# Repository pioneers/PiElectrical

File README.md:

# PiElectrical

This is the working repo for PiElectrical teams

1. [ToDo](#todo)
2. [Repo Structure](#repo-structure)
3. [Setup](#setup)
4. [Work Flow](#work-flow)
5. [How to Create a Gerber](#how-to-create-a-gerber)
6. [Docu Packets](#docu-packets)
7. [FAQ](#faq)
8. [Useful Links](#useful-links)
9. [Standards](#standards)

## ToDo:
* The stuff in PDB-Y16
* Convert motor controller design to KiCad
* Add and test current regulation for motor controller
* Talk to runtime and potentially use cheaper MCU for motor controller

[Back to Top](#pielectrical)

## Repo Structure:

**Boards**: Contains all necessary information about each board, including KiCad (and old Eagle) files, arduino test files, and board specific documentation.

**Bootloaders**: Contains the files necessary to burn the bootloader for boards identifying as Leonardo (Atmega32u4).

**Documentation**: All docu packets and scripts. *Fragile! Do not touch!*

**Production_Files**: Finalized gerbs and other necessary production files (BOM, CPL, etc...) sent out for fabrication.

**Images**: Place all your images in here to enhance your READMEs.

**Libraries**: Necessary KiCad files to work on PiElectrical

ToDo is on the README to keep things easier to see at first glance. GitHub issues tracker can be used as well.

[Back to Top](#pielectrical)

## Setup

<details>
    <summary>When you see an arrow like this... (click me)</summary>
        ...it indicates an expandable section. We usually include images in here as a better reference for you to follow along.
</details>

### Initial Setup of PiElectrical repo on your computer

1. Copy the URL for pioneers/PiElectrical to your clipboard: (Or here: https://github.com/pioneers/PiElectrical.git)
2. In Terminal (Mac, GNU/Linux) or Git Bash (windows), navigate to your working directory (the directory that you want to keep PiElectrical in.)
3. Clone PiElectrical by running this command: `git clone https://github.com/pioneers/PiElectrical.git`

### Installation of KiCad on your computer
1. Download the latest version of KiCad here: https://www.kicad.org/download/
2. <details>
    <summary>Run installer. Use all default settings on installer. (Click to see default settings)<br></summary>
    
</details>

### Setting up KiCad
1. Open KiCad.
2. <details>
    <summary>Depending on whether you've used KiCad before, select the appropriate option on the pop-up. (Default settings if you're new to KiCad).</summary>
    
   </details>

#### Adding Symbols
1. <details>
    <summary>Go to the <i>Preferences</i> tab, and select <i>Manage Symbol Libraries...</i></summary>
    
   </details>
2. <details>
    <summary>If this is your first time using KiCad, it will prompt you to configure the <i>Global Symbol Library</i>. It is highly recommended that you select "Copy default global symbol library table".</summary>
    
   </details>
3. <details>
    <summary>Select the folder icon near the bottom left and navigate to the <i>PiE_Symbols.kicad_sym</i> file in the <i>src</i> folder.</summary>
    
   </details>
4. <details>
    <summary>You should now see the <i>PiE_Symbols</i> in your Symbol Libraries. Make sure the "active" box is checked, and click "OK".</summary>
    
   </details>

#### Adding Footprints
1. <details>
    <summary>Go to the <i>Preferences</i> tab, and select <i>Manage Footprint Libraries...</i></summary>
    
   </details>
2. <details>
    <summary>If this is your first time using KiCad, it will prompt you to configure the <i>Global Footprint Library</i>. It is highly recommended that you select "Copy default global footprint library table".</summary>
    
   </details>
3. <details>
    <summary>Select the folder icon near the bottom left and navigate to the <i>PiE_Footprints.pretty</i> file in the <i>src</i> folder.</summary>
    
   </details>
4. <details>
    <summary>You should now see the <i>PiE_Footprints</i> in your Footprint Libraries. Make sure the "active" box is checked, and click "OK".</summary>
    
   </details>

Note that this setup instruction is based on KiCad 7.0.7, but it should still work for other versions.

[Back to Top](#pielectrical)

## Work Flow

Protocol when working on KiCad files

The revision number should be *REV \<year\>\<revision\>*. E.g. **REV 16A** for year 16 revision A.

If you are not quite familiar with git, see [Useful Links](#useful-links) for the PiE Github tutorial

**WARNING**: Do not modify PiE_Symbols.kicad_sym or PiE_Footprints.pretty without discussing it with PMs.

### Steps when working on KiCad files:

1. In Terminal (mac, GNU/Linux) or GitBash (windows), navigate to your working directory (wherever you have PiElectrical).
2. Make sure your working directory is clean: git status
3. If you haven't started your sub project: git checkout -b YOURNAME-SUBPROJECT
  3. YOUR\_NAME/SUBPROJECT is now the name of your branch
4. Do your work in KiCad.
5. Once you are at a good stopping point in your KiCad work, commit your progress:
    1. git add path/to/your/file
    2. git commit -m "Make your commit message short and with this format"
    3. **NOTE**: Commiting is like saving your file, but for all of PiE as well as your personal computer. And just like saving, Commit Early & Commit Often!
6. Repeat Steps 5 and 6 until you are finished with your EAGLE work.
7. Once you have made your last commit, push your files to the PiElectrical github repo: git push origin YOUR\_BRANCH
    - If you get a merge conflict, contact the PMs for help.
8. If **completely** done, submit a Pull Request

### Commit Message Format Conventions

* Present Tense ("Reroute power traces on team flag", not "Rerouted power traces on team flag")
* No period at the end: ("Reroute power traces on team flag", not "Reroute power traces on team flag.")
* Keep your message length to about one sentence.

### Merge Conflicts: What should I do?

Don't try to fix it yourself: Eagle files are finicky and you might break all your work!

Ask someone who knows how to deal with this, i.e. your PM or something

[Back to Top](#pielectrical)

## Generating Fabrication Outputs

1. Make sure you run the Electrical Rules Check (ERC) in the schematic and the Design Rules Checker (DRC) in the layout, and have no *red* errors. Feel free to ask PMs if you have any questions.
2. <details>
    <summary>Go to File -> Fabrication Outputs -> Gerbers (.gbr)...</summary>
    
   </details>
3. <details>
    <summary>If this is your first time using KiCad, it will prompt you to configure the <i>Global Symbol Library</i>. It is highly recommended that you select "Copy default global symbol library table".</summary>
    
   </details>
4. <details>
    <summary>Select the folder icon near the bottom left and navigate to the <i>PiE_Symbols.kicad_sym</i> file in the <i>src</i> folder.</summary>
    
   </details>
5. <details>
    <summary>You should now see the <i>PiE_Symbols</i> in your Symbol Libraries. Make sure the "active" box is checked, and click "OK".</summary>
    
   </details>

1. Open the brd file
2. Click Cam Job
3. Open pie.cam
4. Make a directory in each sensor's folder called SENSOR\_NAME-gerb
    * SENSOR\_NAME **must** be the exact name as the brd file
5. Run job, and click yes to all for the polygon issue
6. Once all the jobs are done, run `make gerb`

[Back to Top](#pielectrical)

## FAQ

Q: What's the difference between commit before I pull?

A: Do you want to keep any of the changes? Then commit those (the ones you want to keep) before you pull. Or else, the things you pull might conflict with your work, and you'll have a git disaster.

Q: I worked on my stuff, pulled, and everything I did went away!

A: As long as you committed, the PMs can recover your work for you.

Q: Why am I working on my own branch?

A: This is to keep track of pull request and board reviews on a per board basis

[Back to Top](#pielectrical)

## Useful Links

PiE's own [Github Tutorial](https://docs.google.com/a/pioneers.berkeley.edu/presentation/d/1ef5zSDMbE7dCu4XAC4dXhSV5iUd7gjCyXPjRrRvtbQI/edit?usp=sharing)

[PiElectrical Wiki](https://github.com/pioneers/PiElectrical/wiki)

[Markdown Cheatsheet](https://github.com/adam-p/markdown-here/wiki/Markdown-Cheatsheet)

[Arduino Pro Micro Pinouts](https://cdn.sparkfun.com/assets/9/c/3/c/4/523a1765757b7f5c6e8b4567.png)

[BAC DFM](http://instantdfm.bayareacircuits.com/)

Read up on the [PiE Electrical Style Rules and Guidelines](https://staff.pierobotics.org/wiki/Electrical_style_guidelines) (This is a good resource, but outdated)

[Back to Top](#pielectrical)

## Design Rules

You can find JLC's design rules here: https://jlcpcb.com/capabilities/pcb-capabilities. Please review this before ordering a PCB.

#### Some of our general rules:
- Traces **must** be multiples of 45 degrees
- Standard Pin Distance: 100 mils (2.54 mm)

#### Make sure to annotate your boards:

```
Copyright (c) 2023, Pioneers in Engineering
All rights reserved.

Design by: Justin H
This design is open source hardware.
For more information, visit 
github.com/pioneers/PiElectrical
```

[Back to Top](#pielectrical)

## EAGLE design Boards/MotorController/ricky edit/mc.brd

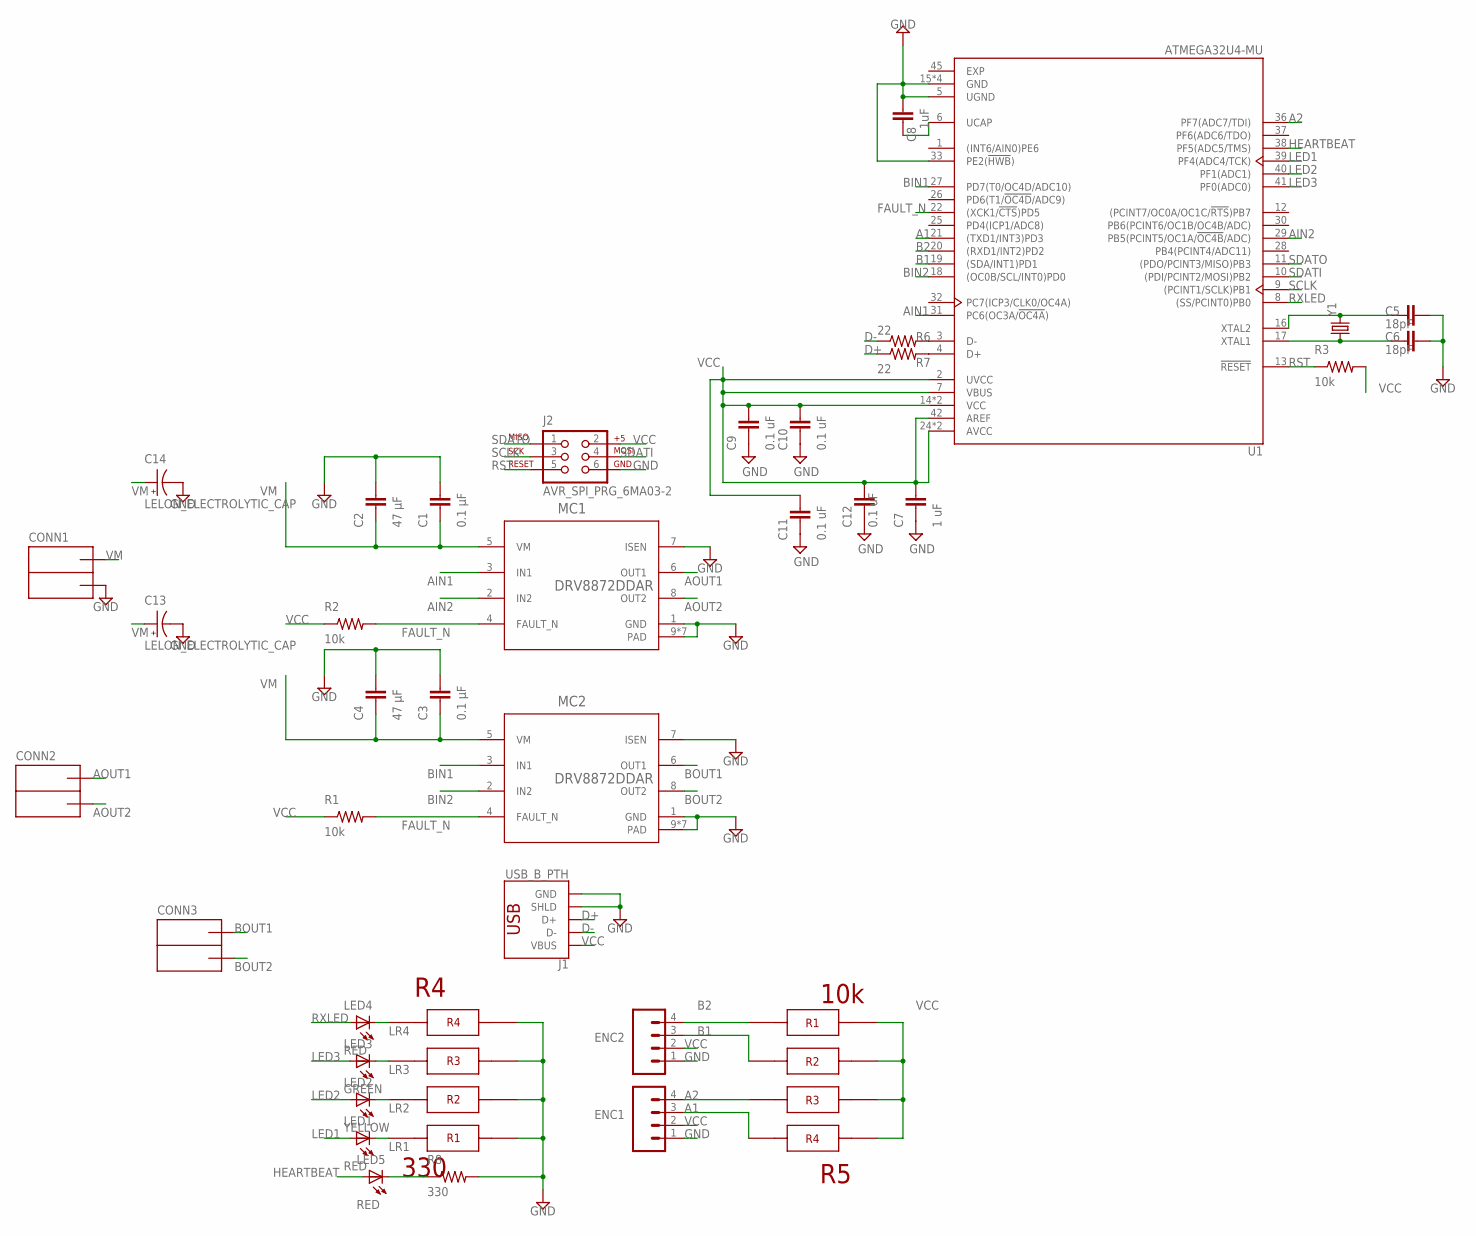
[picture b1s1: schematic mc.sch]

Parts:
C1, C3: 0.1 µF; 0603-CAP
C2, C4: 47 µF; 1206
C5, C6: 18pF; 0603-CAP
C7: 1 uF; 0603-CAP
C8: 1uF; 0603-CAP
C9, C10, C11, C12: 0.1 uF; 0402-CAP
C13, C14: LELON_ELECTROLYTIC_CAP; LELON_CAP
CONN1, CONN2, CONN3: ANDERSONVERTICAL; ANDERSON_VERTICAL
ENC1, ENC2: M041X04-MTA; 1X04-MTA
J1: USB_B_PTH; USB-B-PTH
J2: AVR_SPI_PRG_6MA03-2; MA03-2
LED1, LED4, LED5: RED; LED-0805
LED2: YELLOW; LED-0805
LED3: GREEN; LED-0805
MC1, MC2: DRV8872DDAR; DDA0008H_N_TEX
R1, R2, R3: 10k; R0603
R4: 330; 4X-0603
R5: 10k; 4X-0603
R6, R7: 22; R0603
R8: 330; R0603
U1: ATMEGA32U4-MU; QFN50P700X700X100-45N
Y1: CRYSTAL; CRYSTAL-SMD-5.0X3.2-2PIN

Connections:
A1: ENC1.3, R5.4, U1.21 ((TXD1/INT3)PD3)
A2: ENC1.4, R5.3, U1.36 (PF7(ADC7/TDI))
AIN1: MC1.3 (IN1), U1.31 (PC6(OC3A/!OC4A!))
AIN2: MC1.2 (IN2), U1.29 (PB5(PCINT5/OC1A/!OC4B!/ADC))
AOUT1: CONN2.PIN2 (OUTA), MC1.6 (OUT1)
AOUT2: CONN2.PIN1 (OUTB), MC1.8 (OUT2)
B1: ENC2.3, R5.2, U1.19 ((SDA/INT1)PD1)
B2: ENC2.4, R5.1, U1.20 ((RXD1/INT2)PD2)
BIN1: MC2.3 (IN1), U1.27 (PD7(T0/OC4D/ADC10))
BIN2: MC2.2 (IN2), U1.18 ((OC0B/SCL/INT0)PD0)
BOUT1: CONN3.PIN2 (OUTA), MC2.6 (OUT1)
BOUT2: CONN3.PIN1 (OUTB), MC2.8 (OUT2)
D+: J1.D+, R7.1
D-: J1.D-, R6.1
FAULT_N: MC1.4 (FAULT_N), MC2.4 (FAULT_N), R1.2, R2.2, U1.22 ((XCK1/!CTS!)PD5)
GND: C1.2, C2.2, C3.2, C4.2, C5.2, C6.2, C7.1, C8.2, C9.1, C10.1, C11.1, C12.1, C13.P$2 (-), C14.P$2 (-), CONN1.PIN1 (OUTB), ENC1.1, ENC2.1, J1.GND, J1.SHLD1 (SHLD), J1.SHLD2 (SHLD), J2.6, MC1.1 (GND), MC1.7 (ISEN), MC1.9 (PAD), MC1.P$1 (PAD), MC1.P$2 (PAD), MC1.P$3 (PAD), MC1.P$4 (PAD), MC1.P$5 (PAD), MC1.P$6 (PAD), MC2.1 (GND), MC2.7 (ISEN), MC2.9 (PAD), MC2.P$1 (PAD), MC2.P$2 (PAD), MC2.P$3 (PAD), MC2.P$4 (PAD), MC2.P$5 (PAD), MC2.P$6 (PAD), R4.1, R4.2, R4.3, R4.4, R8.2, U1.5 (UGND), U1.15 (GND), U1.23 (GND), U1.33 (PE2(!HWB!)), U1.35 (GND), U1.43 (GND)
HEARTBEAT: LED5.A, U1.38 (PF5(ADC5/TMS))
LED1: LED1.A, U1.39 (PF4(ADC4/TCK))
LED2: LED2.A, U1.40 (PF1(ADC1))
LED3: LED3.A, U1.41 (PF0(ADC0))
LR1: LED1.C, R4.8
LR2: LED2.C, R4.7
LR3: LED3.C, R4.6
LR4: LED4.C, R4.5
unnamed: C6.1, U1.17 (XTAL1), Y1.P$2 (2)
unnamed: R7.2, U1.4 (D+)
unnamed: R6.2, U1.3 (D-)
unnamed: C8.1, U1.6 (UCAP)
unnamed: C5.1, U1.16 (XTAL2), Y1.P$1 (1)
unnamed: LED5.C, R8.1
RST: J2.5, R3.1, U1.13 (!RESET!)
RXLED: LED4.A, U1.8 ((SS/PCINT0)PB0)
SCLK: J2.3, U1.9 ((PCINT1/SCLK)PB1)
SDATI: J2.4, U1.10 ((PDI/PCINT2/MOSI)PB2)
SDATO: J2.1, U1.11 ((PDO/PCINT3/MISO)PB3)
VCC: C7.2, C9.2, C10.2, C11.2, C12.2, ENC1.2, ENC2.2, J1.VBUS, J2.2, R1.1, R2.1, R3.2, R5.5, R5.6, R5.7, R5.8, U1.2 (UVCC), U1.7 (VBUS), U1.14 (VCC), U1.24 (AVCC), U1.34 (VCC), U1.42 (AREF), U1.44 (AVCC)
VM: C1.1, C2.1, C3.1, C4.1, C13.P$1 (+), C14.P$1 (+), CONN1.PIN2 (OUTA), MC1.5 (VM), MC2.5 (VM)

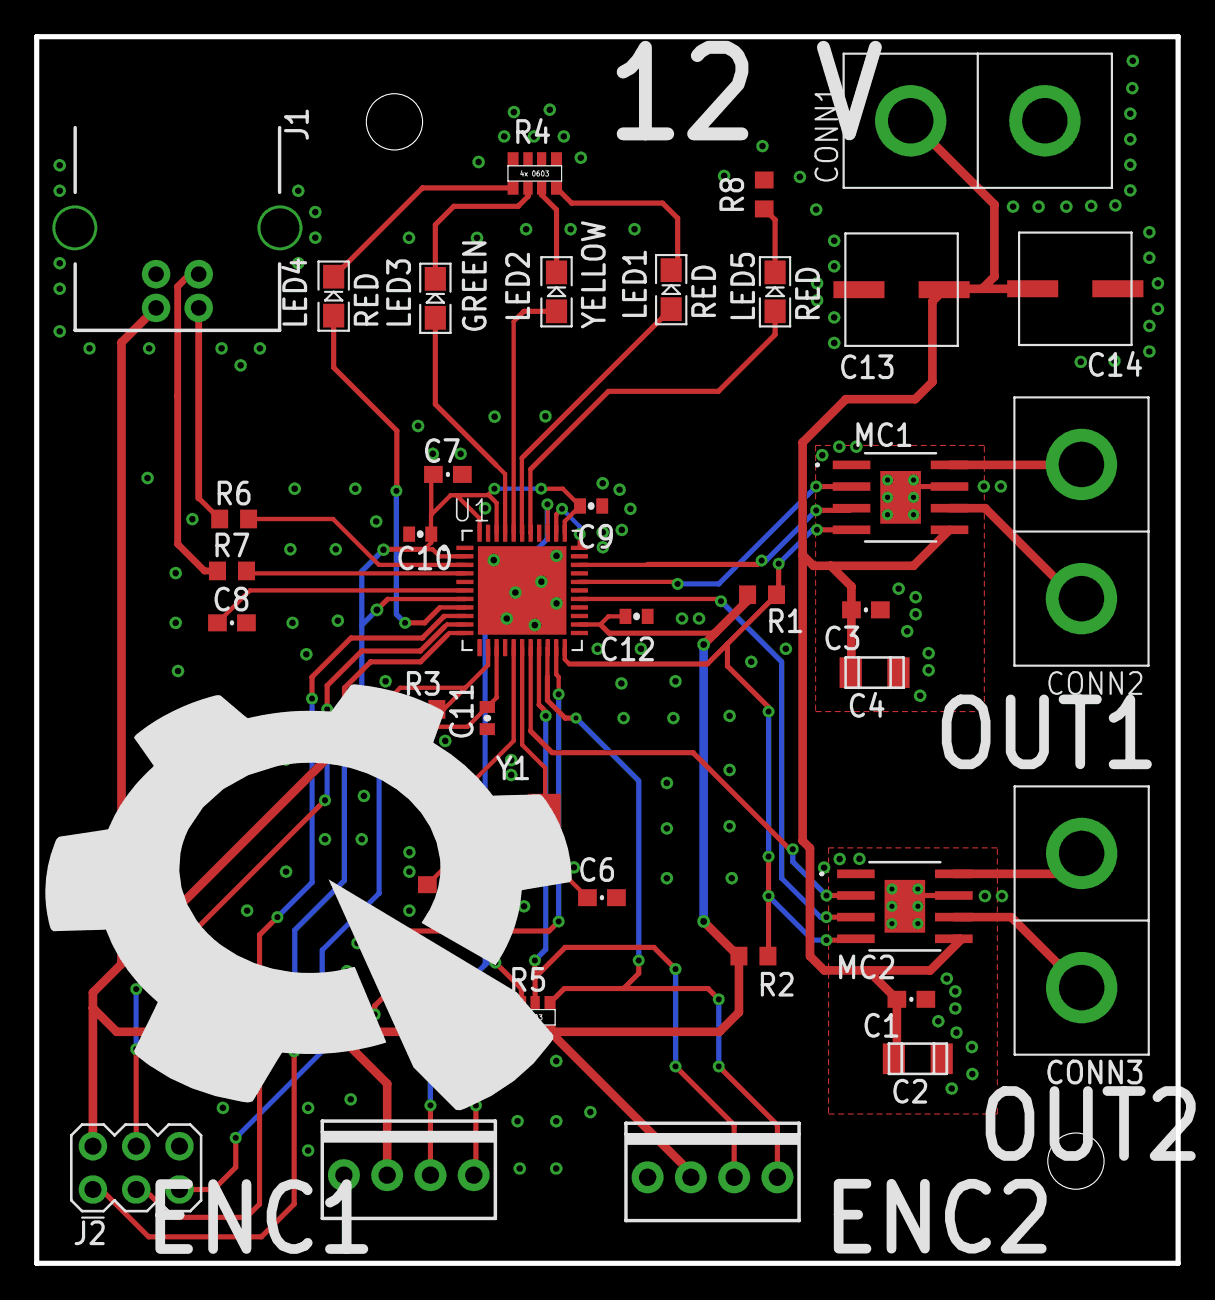
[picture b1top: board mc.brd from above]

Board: 2 copper layers, 67.0 x 72.0 mm, 42 parts (0 on the bottom side), 37 nets.

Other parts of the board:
U$1, U$2, U$4: STAND-OFF
U$5: PIE-LOGO

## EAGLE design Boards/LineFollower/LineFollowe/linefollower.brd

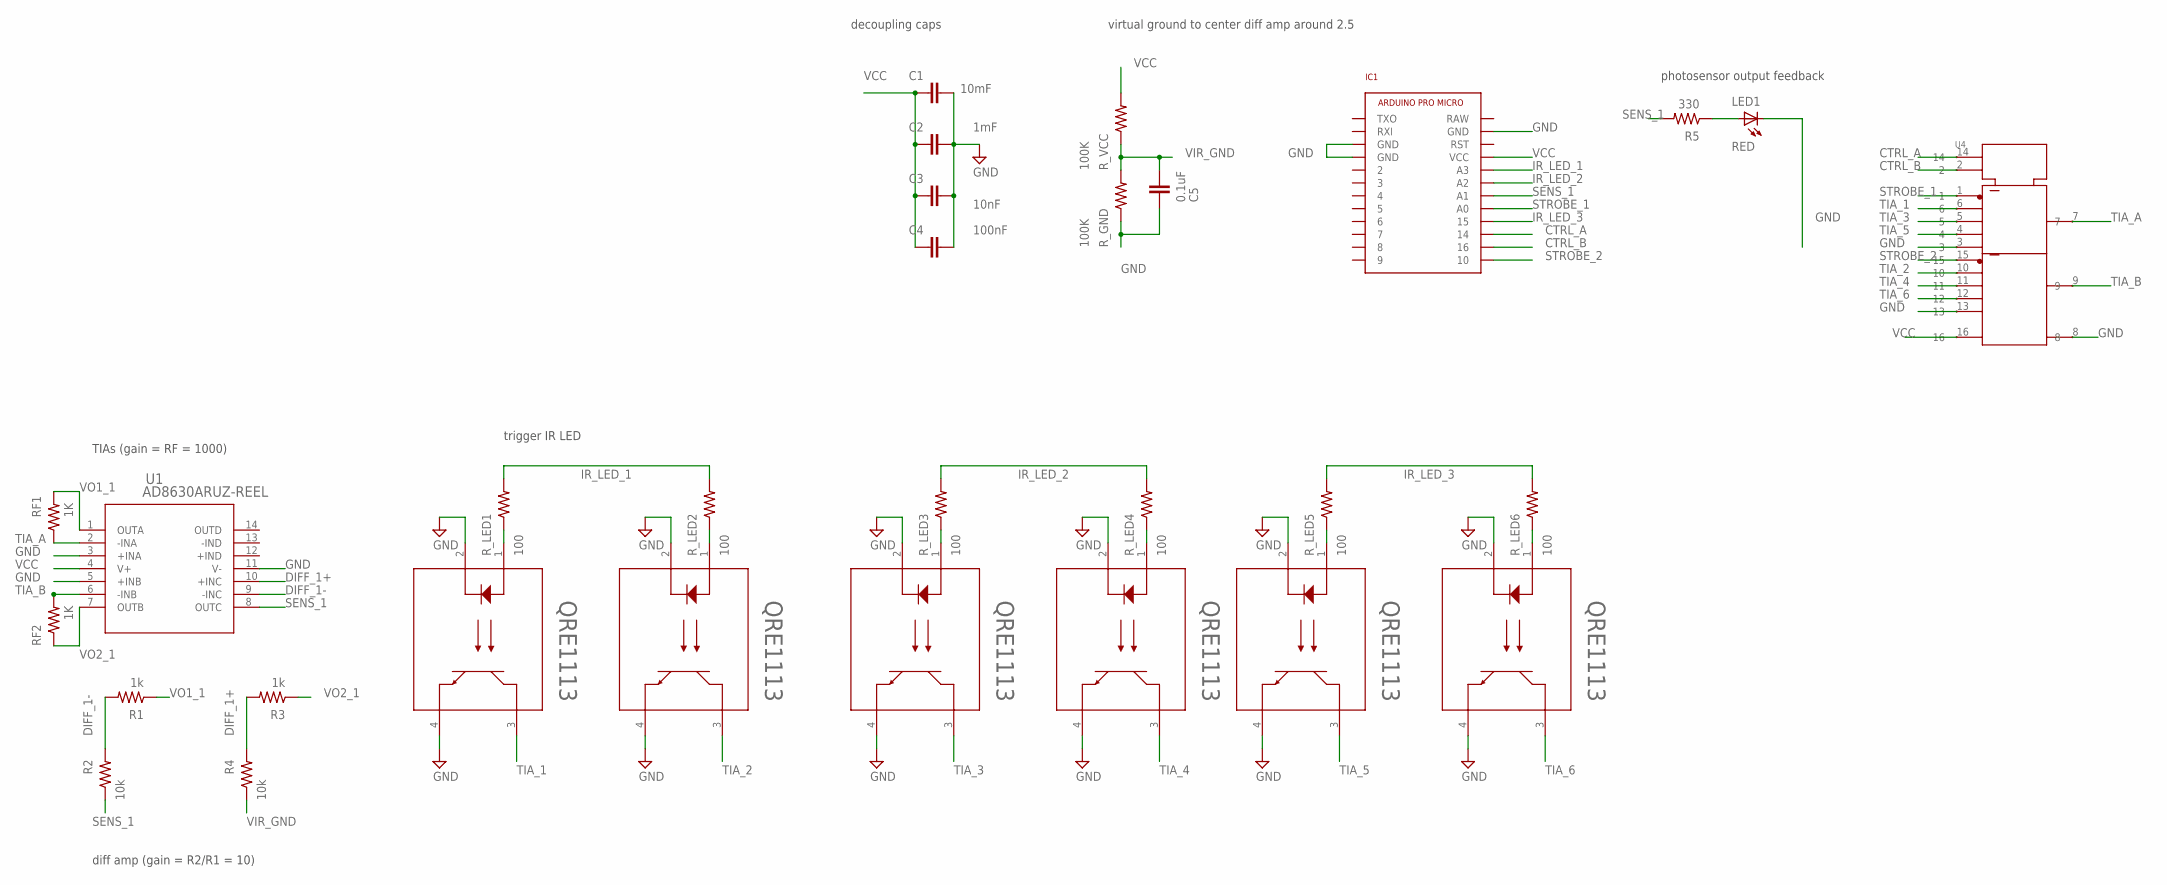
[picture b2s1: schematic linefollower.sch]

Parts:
C1: 10mF; 0402-CAP
C2: 1mF; 0402-CAP
C3: 10nF; 0402-CAP
C4: 100nF; 0402-CAP
C5: 0.1uF; 0402-CAP
IC1: ARDUINO_PRO_MICRO
LED1: RED; LED-0603
Q1, Q2, Q3, Q4, Q5, Q6: QRE1113; DIP4_100AQ_ONS
R1, R3: 1k; R0603
R2, R4: 10k; R0603
R5: 330; R0603
RF1, RF2: 1K; R0603
R_GND: 100K; R0603
R_LED1, R_LED2, R_LED3, R_LED4, R_LED5, R_LED6: 100; R0603
R_VCC: 100K; R0603
U1: AD8630ARUZ-REEL; RU_14_ADI
U4: 74VHC153FT(BJ); TSSOP16B_TOS

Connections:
CTRL_A: IC1.14, U4.14
CTRL_B: IC1.16, U4.2
DIFF_1+: R3.2, R4.2, U1.10 (+INC)
DIFF_1-: R1.2, R2.2, U1.9 (-INC)
GND: C1.2, C2.2, C3.2, C4.2, C5.1, IC1.GND@0 (GND), IC1.GND@1 (GND), IC1.GND@2 (GND), LED1.C, Q1.2, Q1.4, Q2.2, Q2.4, Q3.2, Q3.4, Q4.2, Q4.4, Q5.2, Q5.4, Q6.2, Q6.4, R_GND.1, U1.3 (+INA), U1.5 (+INB), U1.11 (V-), U4.3, U4.8, U4.13
IR_LED_1: IC1.A3, R_LED1.2, R_LED2.2
IR_LED_2: IC1.A2, R_LED3.2, R_LED4.2
IR_LED_3: IC1.15, R_LED5.2, R_LED6.2
unnamed: Q2.1, R_LED2.1
unnamed: LED1.A, R5.1
unnamed: Q1.1, R_LED1.1
unnamed: Q3.1, R_LED3.1
unnamed: Q4.1, R_LED4.1
unnamed: Q5.1, R_LED5.1
unnamed: Q6.1, R_LED6.1
SENS_1: IC1.A1, R2.1, R5.2, U1.8 (OUTC)
STROBE_1: IC1.A0, U4.1
STROBE_2: IC1.10, U4.15
TIA_1: Q1.3, U4.6
TIA_2: Q2.3, U4.10
TIA_3: Q3.3, U4.5
TIA_4: Q4.3, U4.11
TIA_5: Q5.3, U4.4
TIA_6: Q6.3, U4.12
TIA_A: RF1.1, U1.2 (-INA), U4.7
TIA_B: RF2.2, U1.6 (-INB), U4.9
VCC: C1.1, C2.1, C3.1, C4.1, IC1.VCC, R_VCC.2, U1.4 (V+), U4.16
VIR_GND: C5.2, R4.1, R_GND.2, R_VCC.1
VO1_1: R1.1, RF1.2, U1.1 (OUTA)
VO2_1: R3.1, RF2.1, U1.7 (OUTB)

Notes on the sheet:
virtual ground to center diff amp around 2.5
decoupling caps
photosensor output feedback
diff amp (gain = R2/R1 = 10)
TIAs (gain = RF = 1000)
trigger IR LED

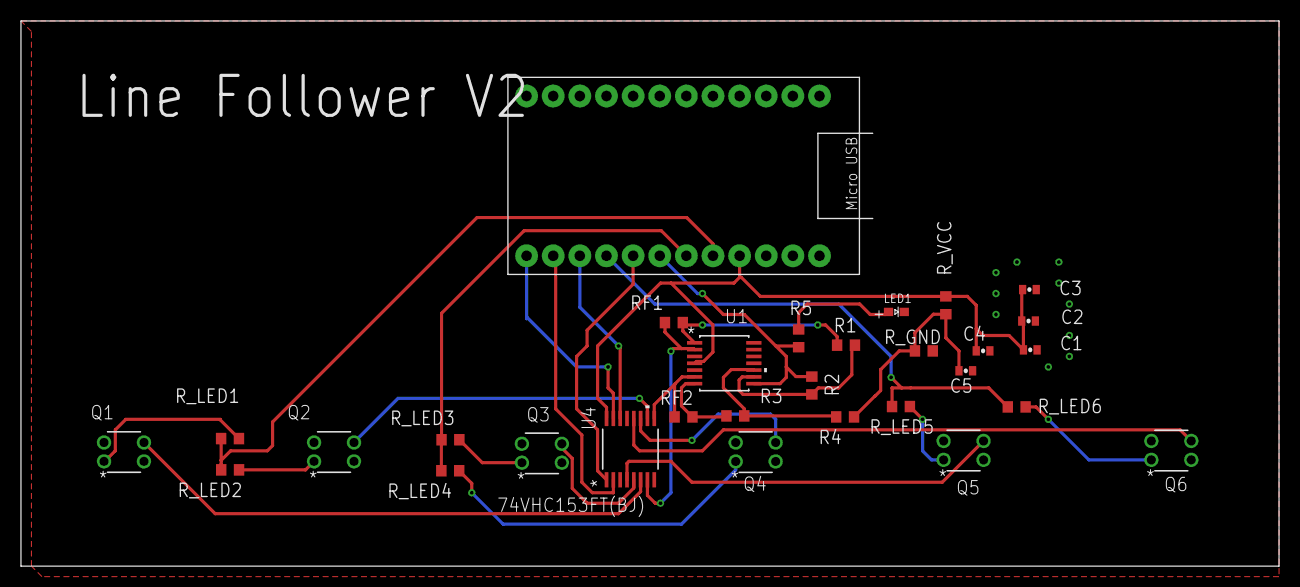
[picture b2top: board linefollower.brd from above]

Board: 2 copper layers, 120.0 x 52.0 mm, 30 parts (0 on the bottom side), 30 nets.

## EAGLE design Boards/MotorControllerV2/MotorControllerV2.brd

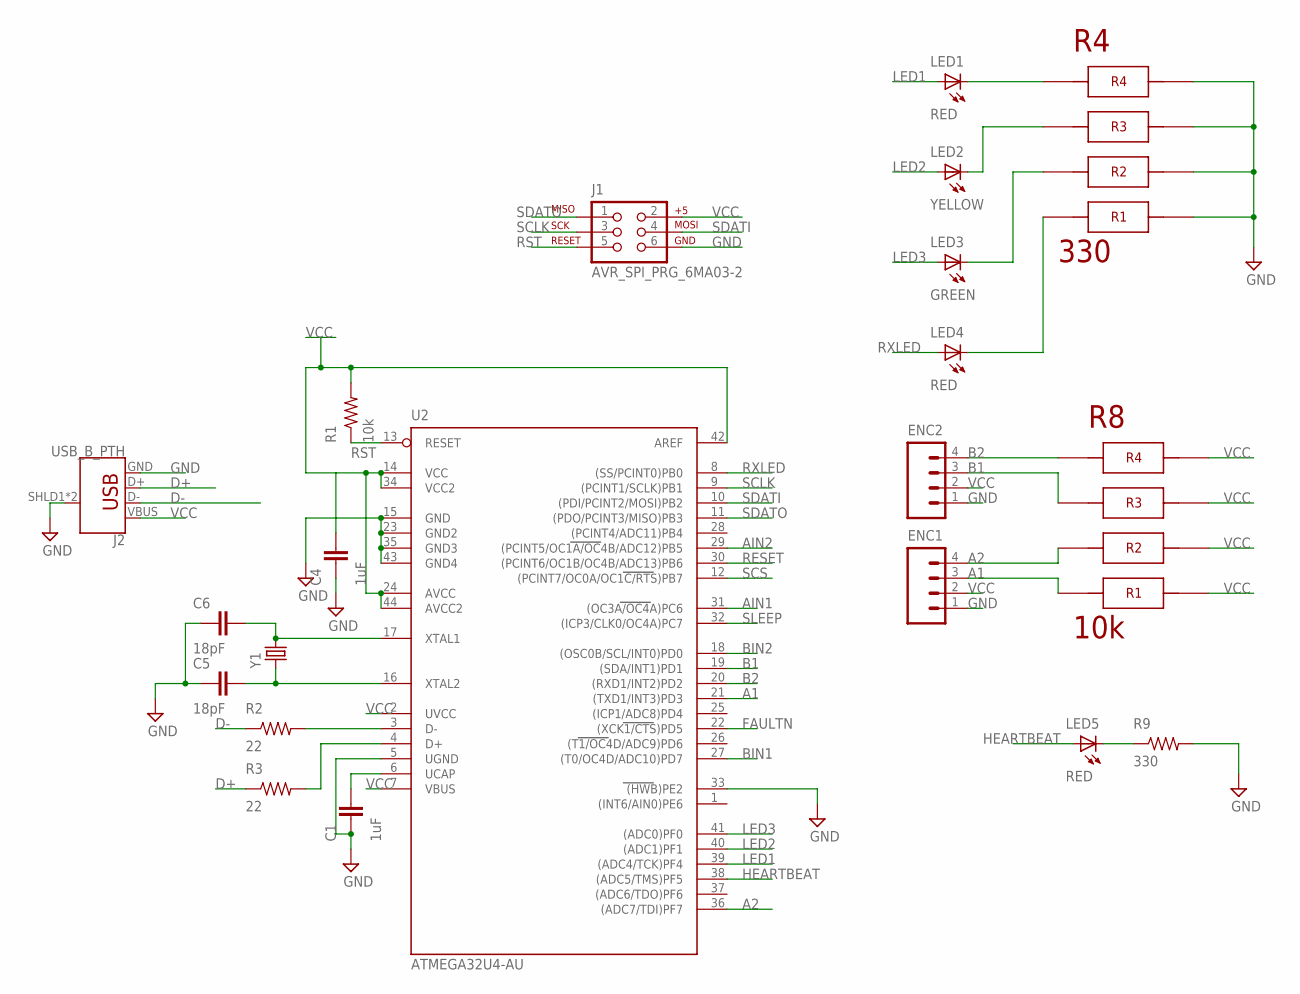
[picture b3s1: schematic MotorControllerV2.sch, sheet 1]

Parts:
C1, C4: 1uF; 0603-CAP
C5, C6: 18pF; 0603-CAP
ENC1, ENC2: M041X04-MTA; 1X04-MTA
J1: AVR_SPI_PRG_6MA03-2; MA03-2
J2: USB_B_PTH; USB-B-PTH
LED1, LED4, LED5: RED; LED-1206
LED2: YELLOW; LED-1206
LED3: GREEN; LED-1206
R1: 10k; R0603
R2, R3: 22; R0603
R4: 330; 4X-0603
R8: 10k; 4X-0603
R9: 330; R0603
U2: ATMEGA32U4-AU; TQFP44
Y1: CRYSTAL10.5X4.8; CRYSTAL-SMD-10.5X4.8-2PIN

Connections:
A1: ENC1.3, R8.8, U2.21 ((TXD1/INT3)PD3)
A2: ENC1.4, R8.7, U2.36 ((ADC7/TDI)PF7)
AIN1: U2.31 ((OC3A/OC4A)PC6); also elsewhere on the board
AIN2: U2.29 ((PCINT5/OC1A/OC4B/ADC12)PB5); also elsewhere on the board
B1: ENC2.3, R8.6, U2.19 ((SDA/INT1)PD1)
B2: ENC2.4, R8.5, U2.20 ((RXD1/INT2)PD2)
BIN1: U2.27 ((T0/OC4D/ADC10)PD7); also elsewhere on the board
BIN2: U2.18 ((OSC0B/SCL/INT0)PD0); also elsewhere on the board
D+: J2.D+, R3.1
D-: J2.D-, R2.1
FAULTN: U2.22 ((XCK1/CTS)PD5); also elsewhere on the board
HEARTBEAT: LED5.A, U2.38 ((ADC5/TMS)PF5)
LED1: LED1.A, U2.39 ((ADC4/TCK)PF4)
LED2: LED2.A, U2.40 ((ADC1)PF1)
LED3: LED3.A, U2.41 ((ADC0)PF0)
unnamed: R2.2, U2.3 (D-)
unnamed: R3.2, U2.4 (D+)
unnamed: LED4.C, R4.8
unnamed: LED1.C, R4.5
unnamed: LED2.C, R4.6
unnamed: LED3.C, R4.7
unnamed: C6.2, U2.17 (XTAL1), Y1.P$2 (2)
unnamed: C5.2, U2.16 (XTAL2), Y1.P$1 (1)
unnamed: LED5.C, R9.1
unnamed: C1.2, U2.6 (UCAP)
RESET: U2.30 ((PCINT6/OC1B/OC4B/ADC13)PB6); also elsewhere on the board
RST: J1.5, R1.1, U2.13 (RESET)
RXLED: LED4.A, U2.8 ((SS/PCINT0)PB0)
SCLK: J1.3, U2.9 ((PCINT1/SCLK)PB1); also elsewhere on the board
SCS: U2.12 ((PCINT7/OC0A/OC1C/RTS)PB7); also elsewhere on the board
SDATI: J1.4, U2.10 ((PDI/PCINT2/MOSI)PB2); also elsewhere on the board
SDATO: J1.1, U2.11 ((PDO/PCINT3/MISO)PB3); also elsewhere on the board
SLEEP: U2.32 ((ICP3/CLK0/OC4A)PC7); also elsewhere on the board
VCC: C4.2, ENC1.2, ENC2.2, J1.2, J2.VBUS, R1.2, R8.1, R8.2, R8.3, R8.4, U2.2 (UVCC), U2.7 (VBUS), U2.14 (VCC), U2.24 (AVCC), U2.34 (VCC2), U2.42 (AREF), U2.44 (AVCC2)

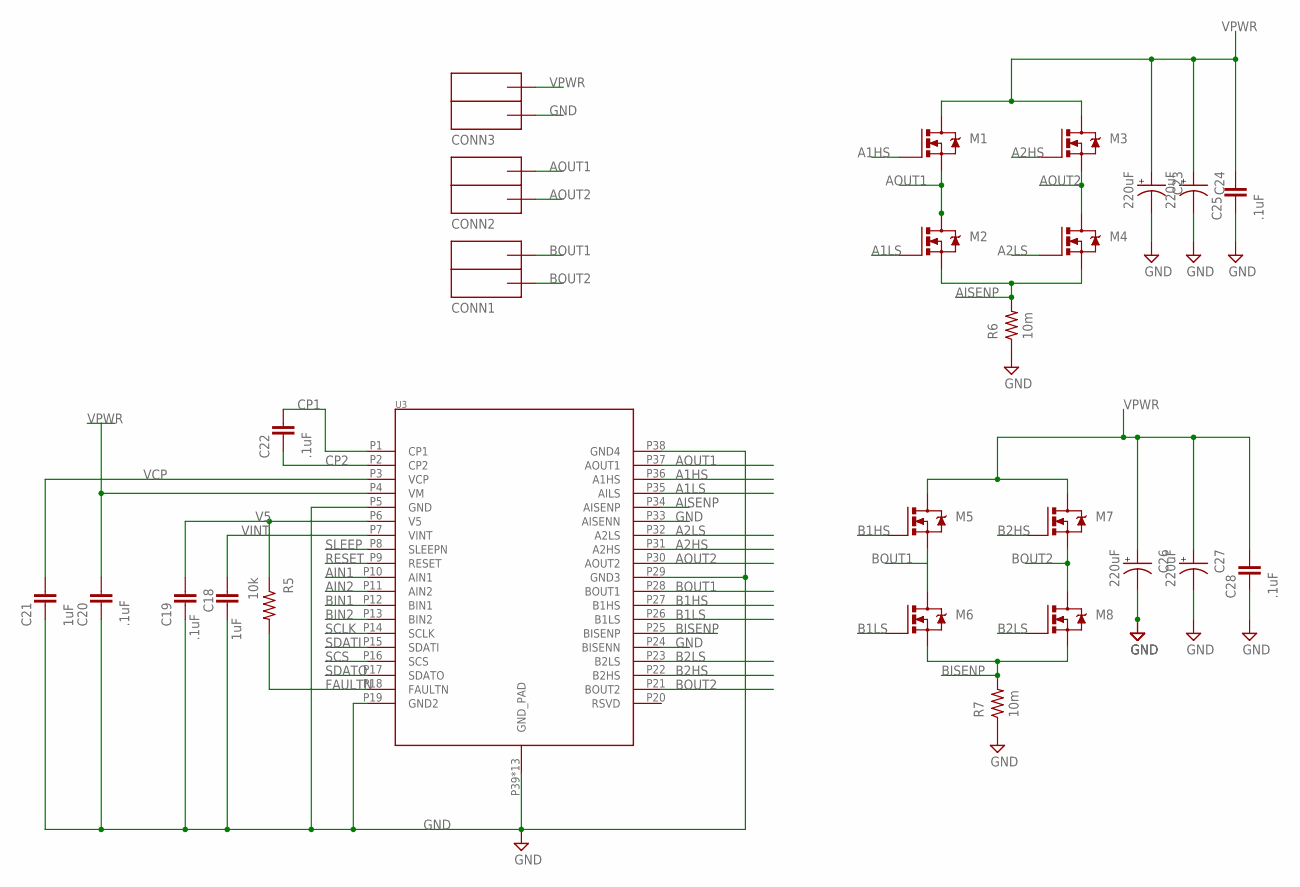
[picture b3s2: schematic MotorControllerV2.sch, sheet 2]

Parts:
C18, C21: 1uF; 0603-CAP
C19, C20, C22, C25, C28: .1uF; 0603-CAP
C23, C24, C26, C27: 220uF; NIPPON_F80
CONN1, CONN2, CONN3: ANDERSONVERTICAL; ANDERSON_VERTICAL
M1, M2, M3, M4, M5, M6, M7, M8: NMOS_CSD17579Q3A; DNH0008A
R5: 10k; R0603
R6, R7: 10m; R2512
U3: DRV8704; HTSSOP(38)

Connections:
A1HS: M1.4 (G), U3.P36 (A1HS)
A1LS: M2.4 (G), U3.P35 (AILS)
A2HS: M3.4 (G), U3.P31 (A2HS)
A2LS: M4.4 (G), U3.P32 (A2LS)
AIN1: U3.P10 (AIN1); also elsewhere on the board
AIN2: U3.P11 (AIN2); also elsewhere on the board
AISENP: M2.1 (S), M2.2 (S), M2.3 (S), M4.1 (S), M4.2 (S), M4.3 (S), R6.2, U3.P34 (AISENP)
AOUT1: CONN2.PIN1 (OUTB), M1.1 (S), M1.2 (S), M1.3 (S), M2.5 (D), M2.6 (D), M2.7 (D), M2.8 (D), M2.9 (D), U3.P37 (AOUT1)
AOUT2: CONN2.PIN2 (OUTA), M3.1 (S), M3.2 (S), M3.3 (S), M4.5 (D), M4.6 (D), M4.7 (D), M4.8 (D), M4.9 (D), U3.P30 (AOUT2)
B1HS: M5.4 (G), U3.P27 (B1HS)
B1LS: M6.4 (G), U3.P26 (B1LS)
B2HS: M7.4 (G), U3.P22 (B2HS)
B2LS: M8.4 (G), U3.P23 (B2LS)
BIN1: U3.P12 (BIN1); also elsewhere on the board
BIN2: U3.P13 (BIN2); also elsewhere on the board
BISENP: M6.1 (S), M6.2 (S), M6.3 (S), M8.1 (S), M8.2 (S), M8.3 (S), R7.2, U3.P25 (BISENP)
BOUT1: CONN1.PIN1 (OUTB), M5.1 (S), M5.2 (S), M5.3 (S), M6.5 (D), M6.6 (D), M6.7 (D), M6.8 (D), M6.9 (D), U3.P28 (BOUT1)
BOUT2: CONN1.PIN2 (OUTA), M7.1 (S), M7.2 (S), M7.3 (S), M8.5 (D), M8.6 (D), M8.7 (D), M8.8 (D), M8.9 (D), U3.P21 (BOUT2)
CP1: C22.2, U3.P1 (CP1)
CP2: C22.1, U3.P2 (CP2)
FAULTN: R5.2, U3.P18 (FAULTN); also elsewhere on the board
RESET: U3.P9 (RESET); also elsewhere on the board
SCLK: U3.P14 (SCLK); also elsewhere on the board
SCS: U3.P16 (SCS); also elsewhere on the board
SDATI: U3.P15 (SDATI); also elsewhere on the board
SDATO: U3.P17 (SDATO); also elsewhere on the board
SLEEP: U3.P8 (SLEEPN); also elsewhere on the board
V5: C19.2, R5.1, U3.P6 (V5)
VINT: C18.2, U3.P7 (VINT)

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
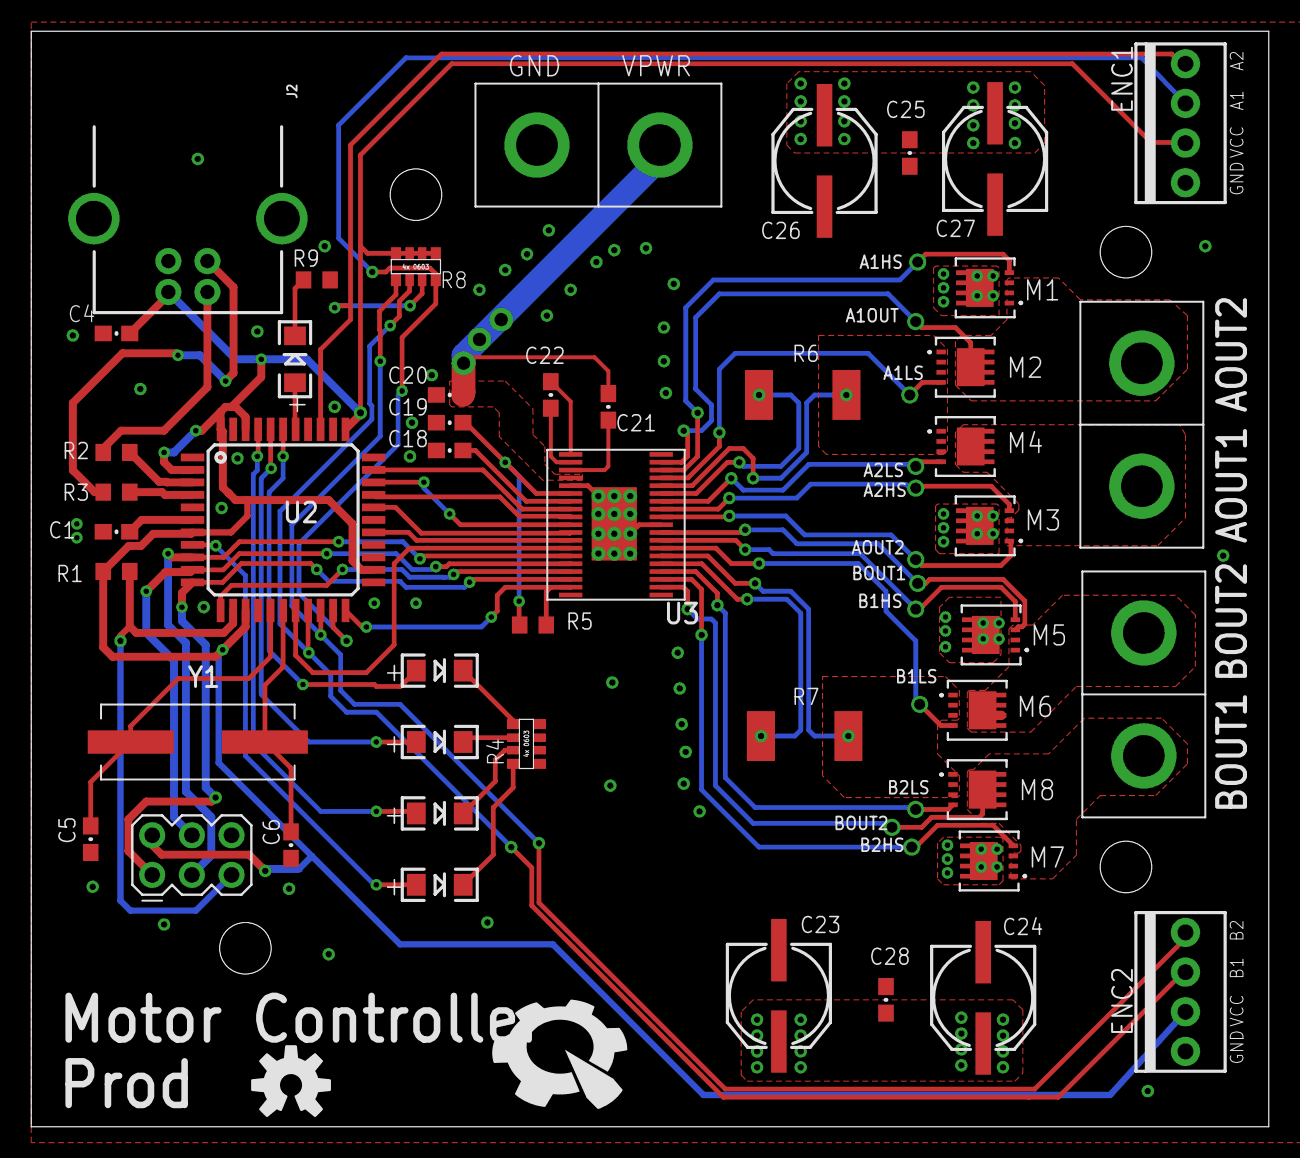
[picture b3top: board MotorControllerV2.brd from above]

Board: 2 copper layers, 79.2 x 70.2 mm, 53 parts (1 on the bottom side), 55 nets.

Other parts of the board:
U$1: PIE-LOGO-SMALL
U$2: OSHW-LOGO-M
U$3, U$4, U$5, U$6: STAND-OFF

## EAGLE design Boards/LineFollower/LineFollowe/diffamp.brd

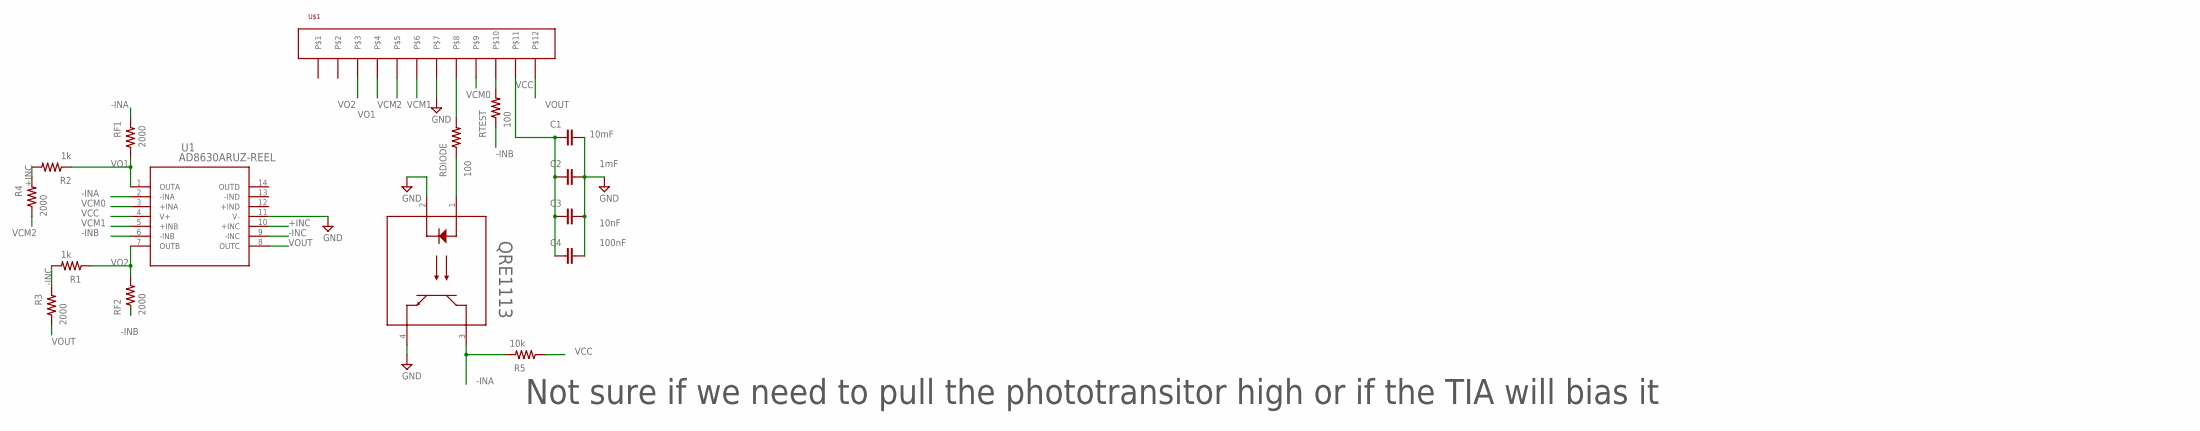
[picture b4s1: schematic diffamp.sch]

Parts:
C1: 10mF; 0402-CAP
C2: 1mF; 0402-CAP
C3: 10nF; 0402-CAP
C4: 100nF; 0402-CAP
Q1: QRE1113; DIP4_100AQ_ONS
R1, R2: 1k; R0603
R3, R4: 2000; R0603
R5: 10k; R0603
RDIODE: 100; R0603
RF1, RF2: 2000; R0603
RTEST: 100; R0603
U1: AD8630ARUZ-REEL; RU_14_ADI
U$1: 12PIN

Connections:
+INC: R2.2, R4.2, U1.10 (+INC)
-INA: Q1.3, R5.2, RF1.2, U1.2 (-INA)
-INB: RF2.1, RTEST.1, U1.6 (-INB)
-INC: R1.2, R3.2, U1.9 (-INC)
GND: C1.2, C2.2, C3.2, C4.2, Q1.2, Q1.4, U1.11 (V-), U$1.P$7
unnamed: RDIODE.2, U$1.P$8
unnamed: Q1.1, RDIODE.1
unnamed: RTEST.2, U$1.P$10
VCC: C1.1, C2.1, C3.1, C4.1, R5.1, U1.4 (V+), U$1.P$11
VCM0: U1.3 (+INA), U$1.P$9
VCM1: U1.5 (+INB), U$1.P$6
VCM2: R4.1, U$1.P$5
VO1: R2.1, RF1.1, U1.1 (OUTA), U$1.P$4
VO2: R1.1, RF2.2, U1.7 (OUTB), U$1.P$3
VOUT: R3.1, U1.8 (OUTC), U$1.P$12

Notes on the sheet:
Not sure if we need to pull the phototransitor high or if the TIA will bias it

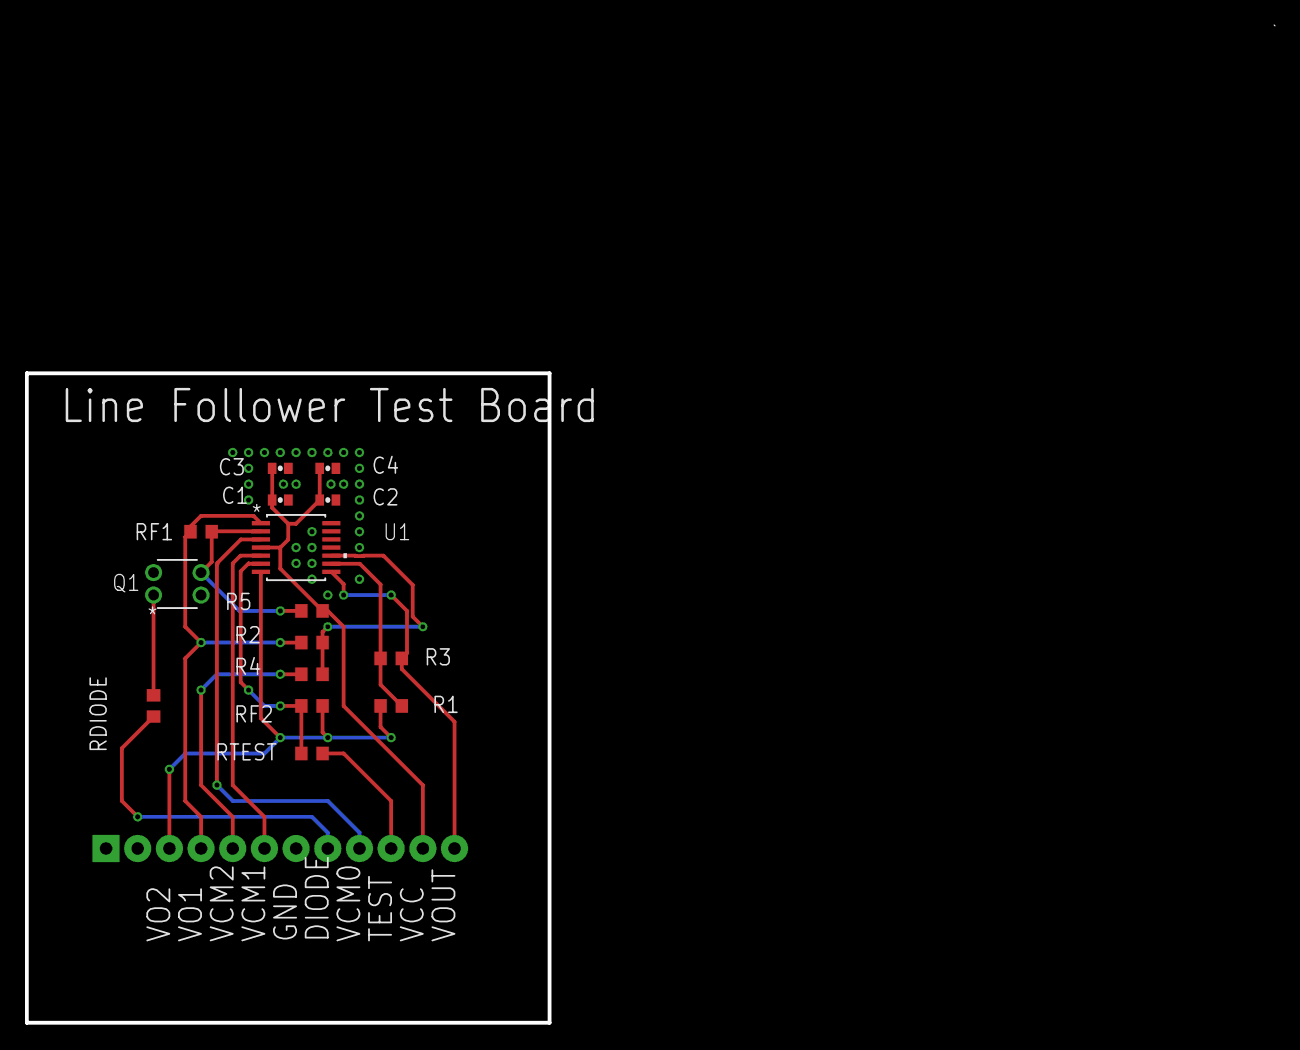
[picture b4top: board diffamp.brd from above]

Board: 2 copper layers, 41.9 x 52.1 mm, 16 parts (0 on the bottom side), 15 nets.

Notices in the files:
parts and their libraries:
COPYRIGHT: Copyright (C) 2018 Accelerated Designs. All rights reserved
COPYRIGHT: Copyright (C) 2016 Accelerated Designs. All rights reserved
SparkFun-Connectors: Licensing: Creative Commons ShareAlike 4.0 International - https://creativecommons.org/licenses/by-sa/4.0
